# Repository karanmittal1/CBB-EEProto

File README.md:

CBB-EEProto
===========

This repository contains the design files for the Logic Supply CBB-EEProto Cape for the 
BeagleBone and BeagleBone Black. 

Check out the CBB-EEProto Cape at http://www.logicsupply.com/cbb-eeproto/

----

Follow us on Google+ for updates and more information: https://plus.google.com/u/0/b/103613886667848850929/

Created by Alexander Hiam for Logic Supply.

This work is licensed under the Creative Commons Attribution-Share Alike 3.0 Unported License. 
To view a copy of this license, visit http://creativecommons.org/licenses/by-sa/3.0/ or send a 
letter to Creative Commons, 171 Second Street, Suite 300, San Francisco, California, 94105, USA.

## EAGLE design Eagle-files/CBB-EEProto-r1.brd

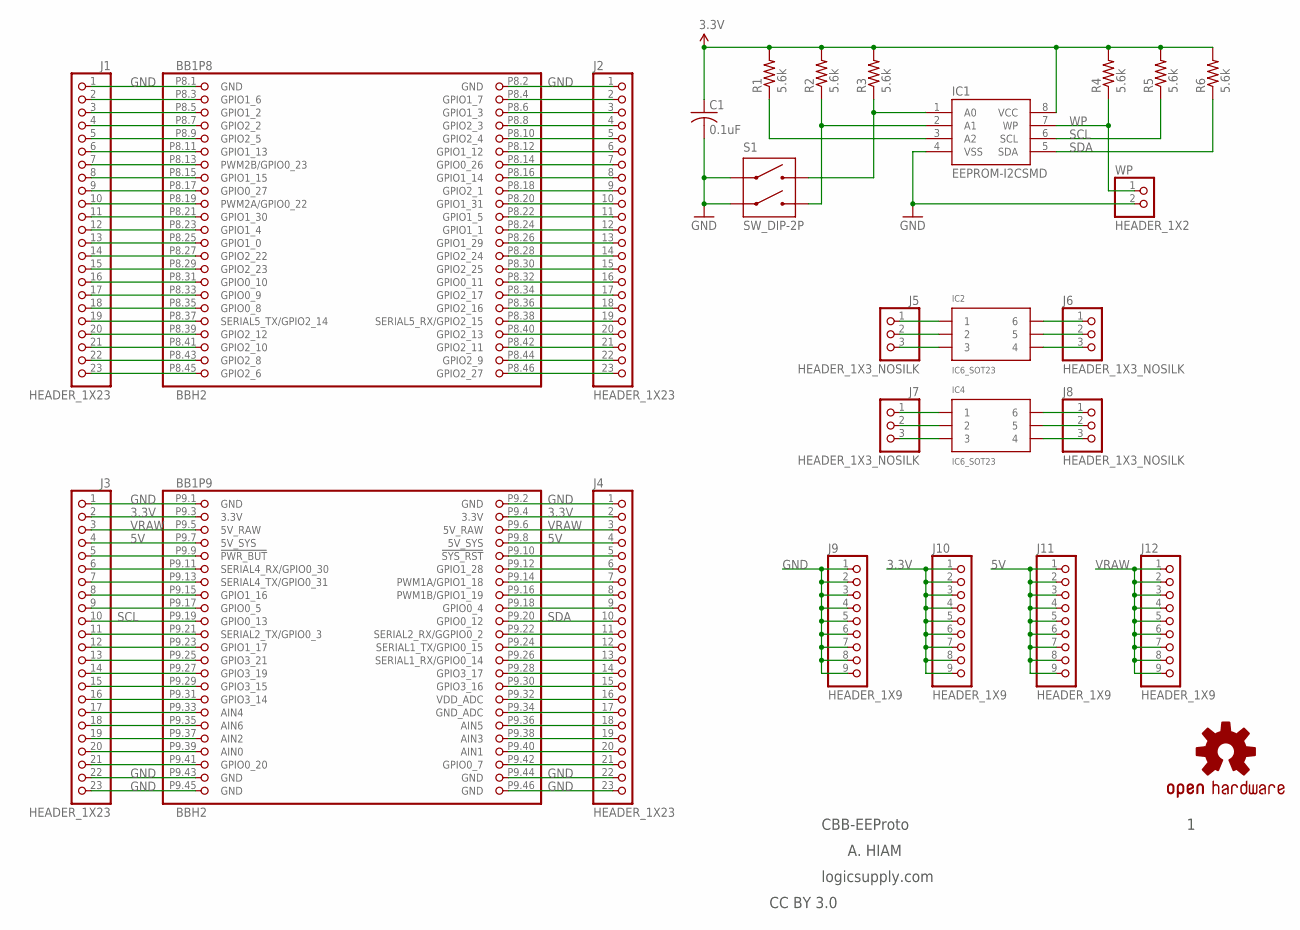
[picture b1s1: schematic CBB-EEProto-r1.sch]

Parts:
BB1: BBH2; BB_CAPE_TOP
C1: 0.1uF; C0603
IC1: EEPROM-I2CSMD; SO08
IC2, IC4: IC6_SOT23; SOT23-6
J1, J2, J3, J4: HEADER_1X23
J5, J6, J7, J8: HEADER_1X3_NOSILK
J9, J10, J11, J12: HEADER_1X9
R1, R2, R3, R4, R5, R6: 5.6k; R0603
S1: SW_DIP-2P; DIPSWITCH-2P-SMD-1.27; PARTNO EHS102LD
U$3: OSHW-LOGOS; OSHW-LOGO-S
WP: HEADER_1X2

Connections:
3.3V: BB1.P9.3 (3.3V), BB1.P9.4 (3.3V), C1.1, IC1.8 (VCC), J3.2, J4.2, J10.1, J10.2, J10.3, J10.4, J10.5, J10.6, J10.7, J10.8, J10.9, R1.2, R2.2, R3.2, R4.2, R5.2, R6.2
5V: BB1.P9.7 (5V_SYS), BB1.P9.8 (5V_SYS), J3.4, J4.4, J11.1, J11.2, J11.3, J11.4, J11.5, J11.6, J11.7, J11.8, J11.9
GND: BB1.P8.1 (GND), BB1.P8.2 (GND), BB1.P9.1 (GND), BB1.P9.2 (GND), BB1.P9.43 (GND), BB1.P9.44 (GND), BB1.P9.45 (GND), BB1.P9.46 (GND), C1.2, IC1.4 (VSS), J1.1, J2.1, J3.1, J3.22, J3.23, J4.1, J4.22, J4.23, J9.1, J9.2, J9.3, J9.4, J9.5, J9.6, J9.7, J9.8, J9.9, S1.1A, S1.2A, WP.2
unnamed: BB1.P8.4 (GPIO1_7), J2.2
unnamed: BB1.P8.6 (GPIO1_3), J2.3
unnamed: BB1.P8.8 (GPIO2_3), J2.4
unnamed: BB1.P8.10 (GPIO2_4), J2.5
unnamed: BB1.P8.12 (GPIO1_12), J2.6
unnamed: BB1.P8.14 (GPIO0_26), J2.7
unnamed: BB1.P8.16 (GPIO1_14), J2.8
unnamed: BB1.P8.18 (GPIO2_1), J2.9
unnamed: BB1.P8.20 (GPIO1_31), J2.10
unnamed: BB1.P8.22 (GPIO1_5), J2.11
unnamed: BB1.P8.24 (GPIO1_1), J2.12
unnamed: BB1.P8.26 (GPIO1_29), J2.13
unnamed: BB1.P8.28 (GPIO2_24), J2.14
unnamed: BB1.P8.30 (GPIO2_25), J2.15
unnamed: BB1.P8.32 (GPIO0_11), J2.16
unnamed: BB1.P8.34 (GPIO2_17), J2.17
unnamed: BB1.P8.36 (GPIO2_16), J2.18
unnamed: BB1.P8.38 (SERIAL5_RX/GPIO2_15), J2.19
unnamed: BB1.P8.40 (GPIO2_13), J2.20
unnamed: BB1.P8.42 (GPIO2_11), J2.21
unnamed: BB1.P8.44 (GPIO2_9), J2.22
unnamed: BB1.P8.46 (GPIO2_27), J2.23
unnamed: BB1.P8.45 (GPIO2_6), J1.23
unnamed: BB1.P8.43 (GPIO2_8), J1.22
unnamed: BB1.P8.41 (GPIO2_10), J1.21
unnamed: BB1.P8.39 (GPIO2_12), J1.20
unnamed: BB1.P8.37 (SERIAL5_TX/GPIO2_14), J1.19
unnamed: BB1.P8.35 (GPIO0_8), J1.18
unnamed: BB1.P8.33 (GPIO0_9), J1.17
unnamed: BB1.P8.31 (GPIO0_10), J1.16
unnamed: BB1.P8.29 (GPIO2_23), J1.15
unnamed: BB1.P8.27 (GPIO2_22), J1.14
unnamed: BB1.P8.25 (GPIO1_0), J1.13
unnamed: BB1.P8.23 (GPIO1_4), J1.12
unnamed: BB1.P8.21 (GPIO1_30), J1.11
unnamed: BB1.P8.19 (PWM2A/GPIO0_22), J1.10
unnamed: BB1.P8.17 (GPIO0_27), J1.9
unnamed: BB1.P8.15 (GPIO1_15), J1.8
unnamed: BB1.P8.13 (PWM2B/GPIO0_23), J1.7
unnamed: BB1.P8.11 (GPIO1_13), J1.6
unnamed: BB1.P8.9 (GPIO2_5), J1.5
unnamed: BB1.P8.7 (GPIO2_2), J1.4
unnamed: BB1.P8.5 (GPIO1_2), J1.3
unnamed: BB1.P8.3 (GPIO1_6), J1.2
unnamed: BB1.P9.41 (GPIO0_20), J3.21
unnamed: BB1.P9.39 (AIN0), J3.20
unnamed: BB1.P9.37 (AIN2), J3.19
unnamed: BB1.P9.35 (AIN6), J3.18
unnamed: BB1.P9.33 (AIN4), J3.17
unnamed: BB1.P9.31 (GPIO3_14), J3.16
unnamed: BB1.P9.29 (GPIO3_15), J3.15
unnamed: BB1.P9.27 (GPIO3_19), J3.14
unnamed: BB1.P9.25 (GPIO3_21), J3.13
unnamed: BB1.P9.23 (GPIO1_17), J3.12
unnamed: BB1.P9.21 (SERIAL2_TX/GPIO0_3), J3.11
unnamed: BB1.P9.17 (GPIO0_5), J3.9
unnamed: BB1.P9.15 (GPIO1_16), J3.8
unnamed: BB1.P9.13 (SERIAL4_TX/GPIO0_31), J3.7
unnamed: BB1.P9.11 (SERIAL4_RX/GPIO0_30), J3.6
unnamed: BB1.P9.9 (!PWR_BUT), J3.5
unnamed: BB1.P9.10 (!SYS_RST), J4.5
unnamed: BB1.P9.12 (GPIO1_28), J4.6
unnamed: BB1.P9.14 (PWM1A/GPIO1_18), J4.7
unnamed: BB1.P9.16 (PWM1B/GPIO1_19), J4.8
unnamed: BB1.P9.18 (GPIO0_4), J4.9
unnamed: BB1.P9.22 (SERIAL2_RX/GGPIO0_2), J4.11
unnamed: BB1.P9.24 (SERIAL1_TX/GPIO0_15), J4.12
unnamed: BB1.P9.26 (SERIAL1_RX/GPIO0_14), J4.13
unnamed: BB1.P9.28 (GPIO3_17), J4.14
unnamed: BB1.P9.30 (GPIO3_16), J4.15
unnamed: BB1.P9.32 (VDD_ADC), J4.16
unnamed: BB1.P9.34 (GND_ADC), J4.17
unnamed: BB1.P9.36 (AIN5), J4.18
unnamed: BB1.P9.38 (AIN3), J4.19
unnamed: BB1.P9.40 (AIN1), J4.20
unnamed: BB1.P9.42 (GPIO0_7), J4.21
unnamed: IC2.1, J5.1
unnamed: IC2.2, J5.2
unnamed: IC2.3, J5.3
unnamed: IC2.6, J6.1
unnamed: IC2.5, J6.2
unnamed: IC2.4, J6.3
unnamed: IC4.1, J7.1
unnamed: IC4.2, J7.2
unnamed: IC4.3, J7.3
unnamed: IC4.6, J8.1
unnamed: IC4.5, J8.2
unnamed: IC4.4, J8.3
unnamed: IC1.1 (A0), R3.1, S1.1B
unnamed: IC1.2 (A1), R2.1, S1.2B
unnamed: IC1.3 (A2), R1.1
SCL: BB1.P9.19 (GPIO0_13), IC1.6 (SCL), J3.10, R5.1
SDA: BB1.P9.20 (GPIO0_12), IC1.5 (SDA), J4.10, R6.1
VRAW: BB1.P9.5 (5V_RAW), BB1.P9.6 (5V_RAW), J3.3, J4.3, J12.1, J12.2, J12.3, J12.4, J12.5, J12.6, J12.7, J12.8, J12.9
WP: IC1.7 (WP), R4.1, WP.1

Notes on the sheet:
A. HIAM
CBB-EEProto
logicsupply.com
CC BY 3.0

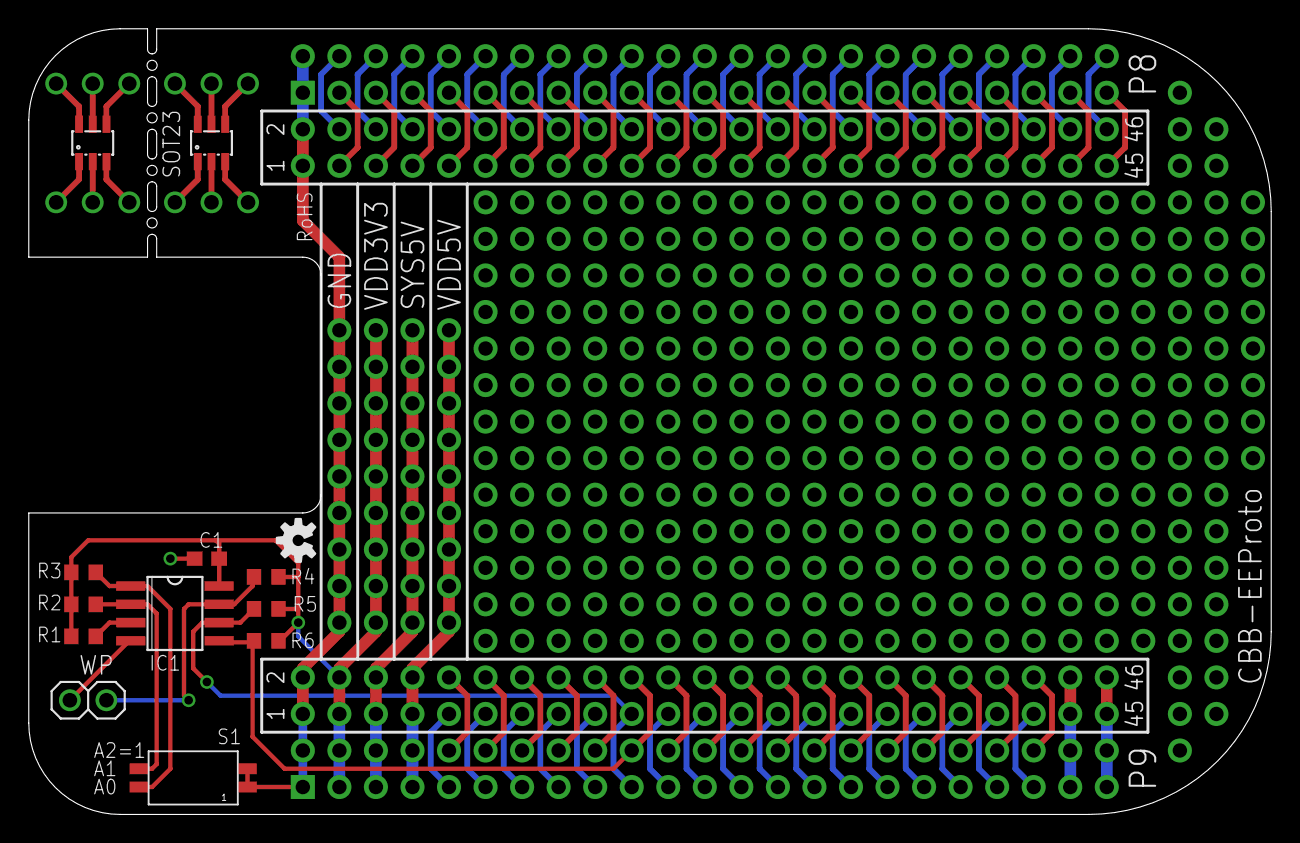
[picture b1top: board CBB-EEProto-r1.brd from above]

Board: 2 copper layers, 86.4 x 54.6 mm, 26 parts (1 on the bottom side), 98 nets.

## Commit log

2013-11-26 added Eagle files
2013-11-26 readme
2013-12-18 added manual
2013-12-18 update product link
2013-12-20 fixed typo

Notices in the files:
parts and their libraries:
SparkFun-Aesthetics: Licensing: CC v3.0 Share-Alike You are welcome to use this library for commercial purposes.
